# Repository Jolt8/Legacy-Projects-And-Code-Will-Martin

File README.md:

# A Repo for personal projects 

This is a repo for all the pieces of code I've written while learning chemical engineering.

Many of my python projects are quite old as I have switched to Julia. 

The only thing I haven't ported to Julia from python is my old and incomplete process simulator and my MESH distillation solver. 

Most of the work I've done recently has revolved around solving ODEs, PDEs in Julia as well as working ModelingToolkit.jl

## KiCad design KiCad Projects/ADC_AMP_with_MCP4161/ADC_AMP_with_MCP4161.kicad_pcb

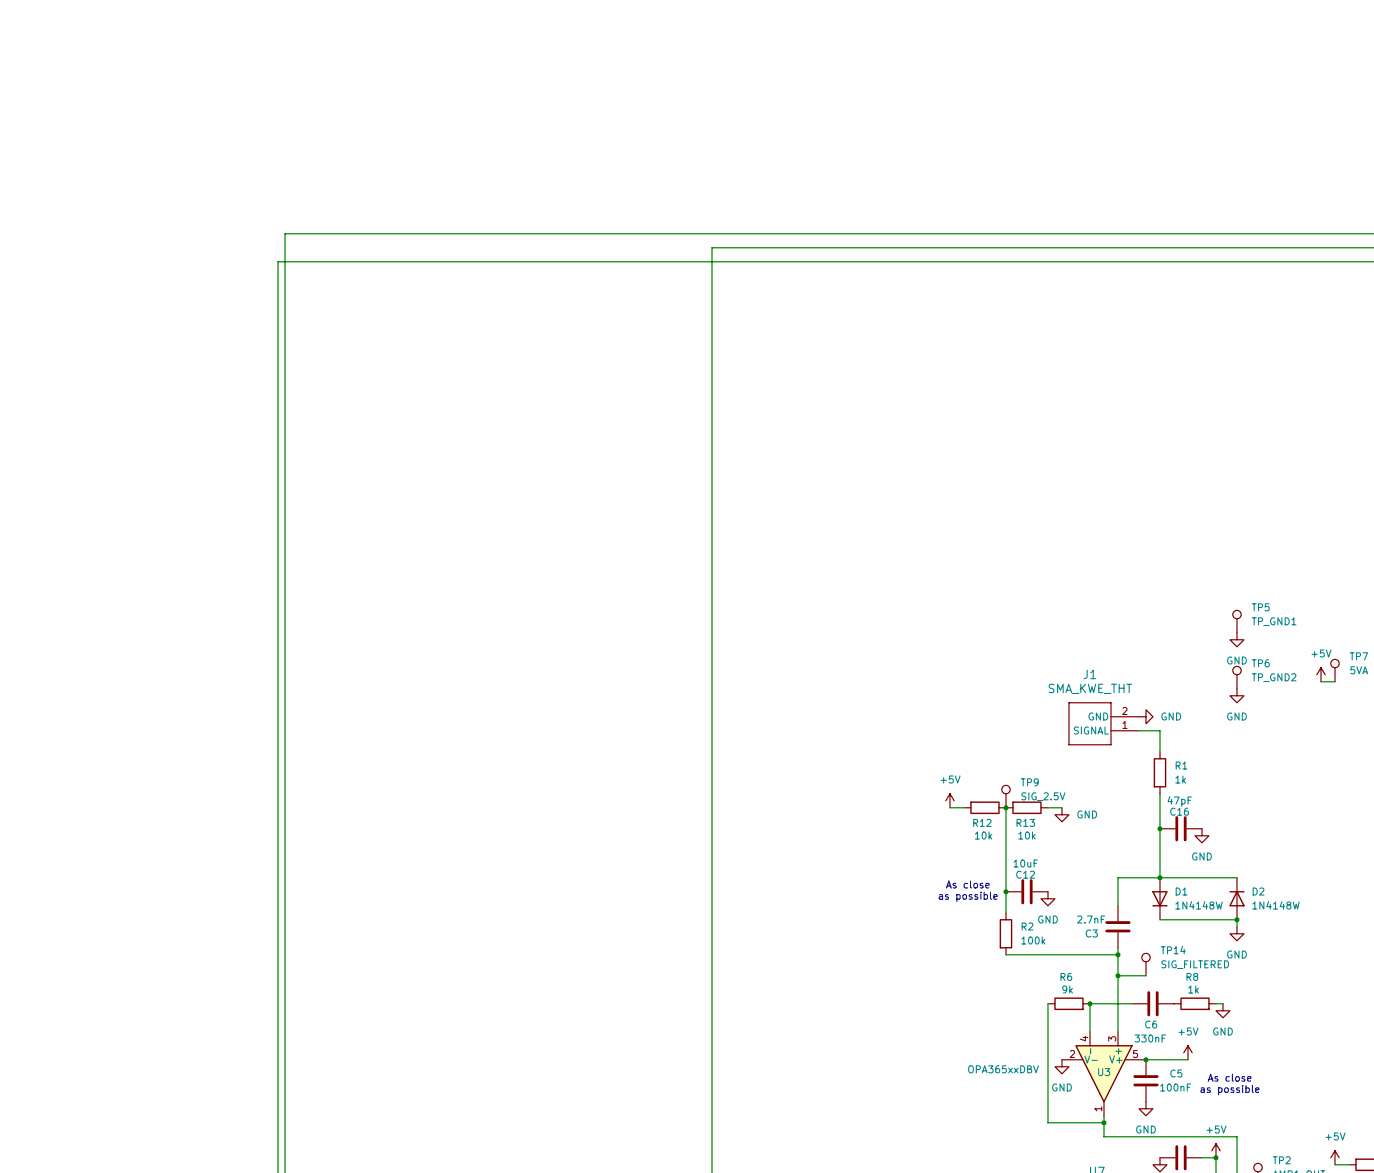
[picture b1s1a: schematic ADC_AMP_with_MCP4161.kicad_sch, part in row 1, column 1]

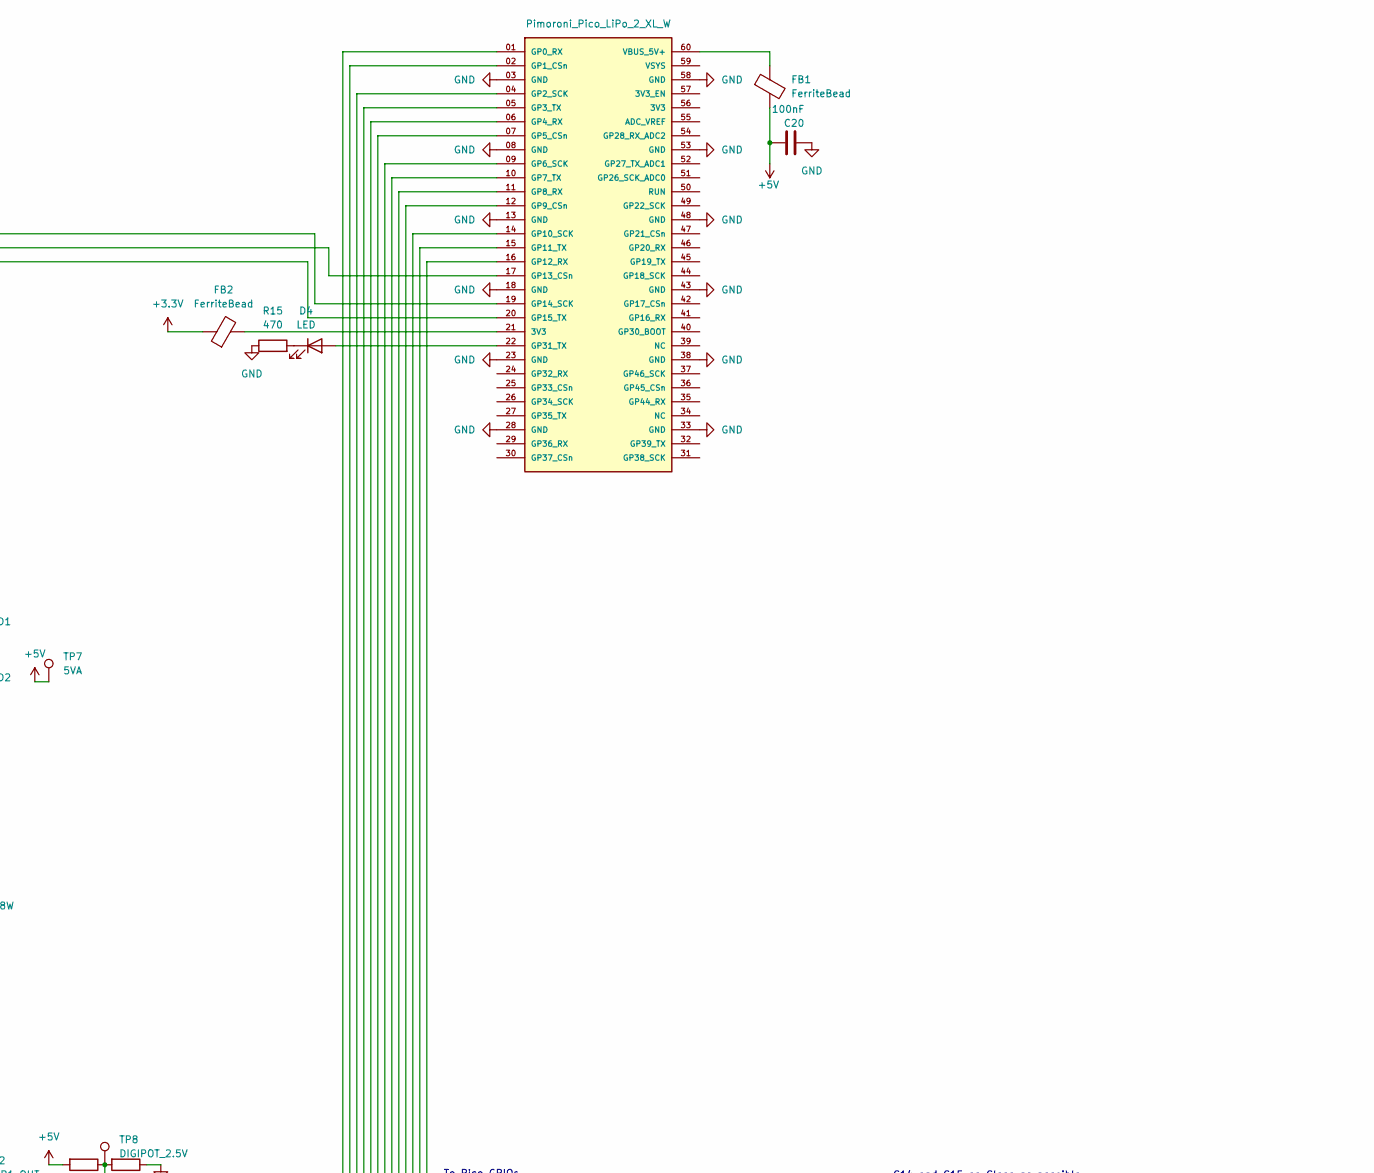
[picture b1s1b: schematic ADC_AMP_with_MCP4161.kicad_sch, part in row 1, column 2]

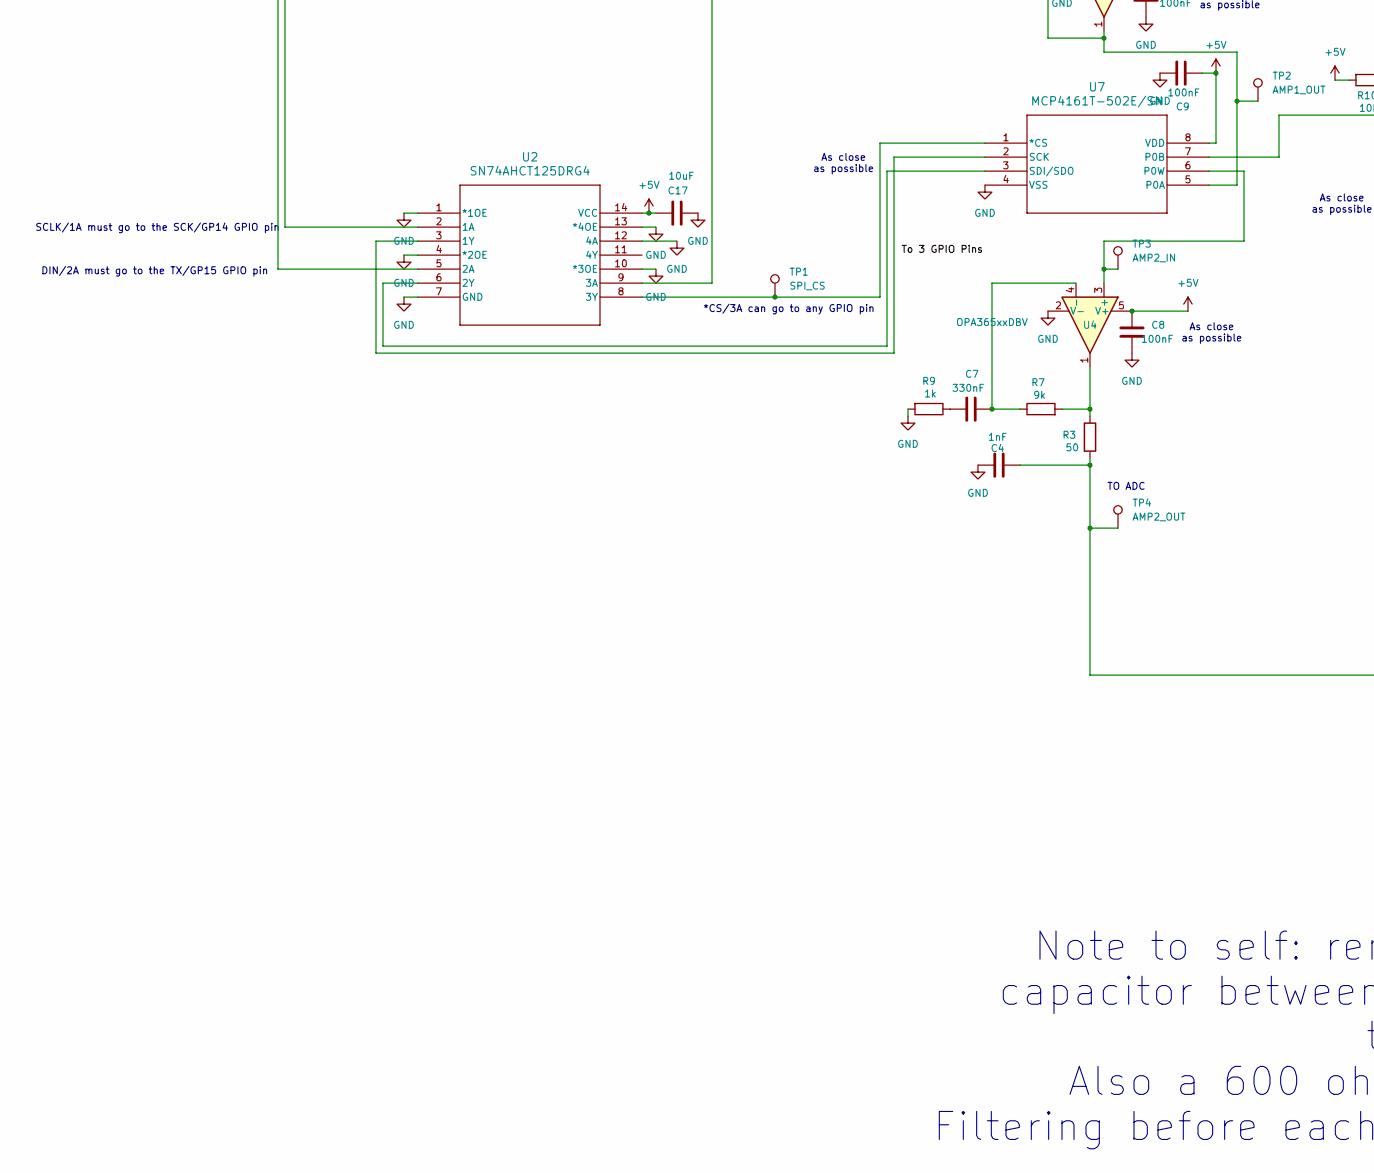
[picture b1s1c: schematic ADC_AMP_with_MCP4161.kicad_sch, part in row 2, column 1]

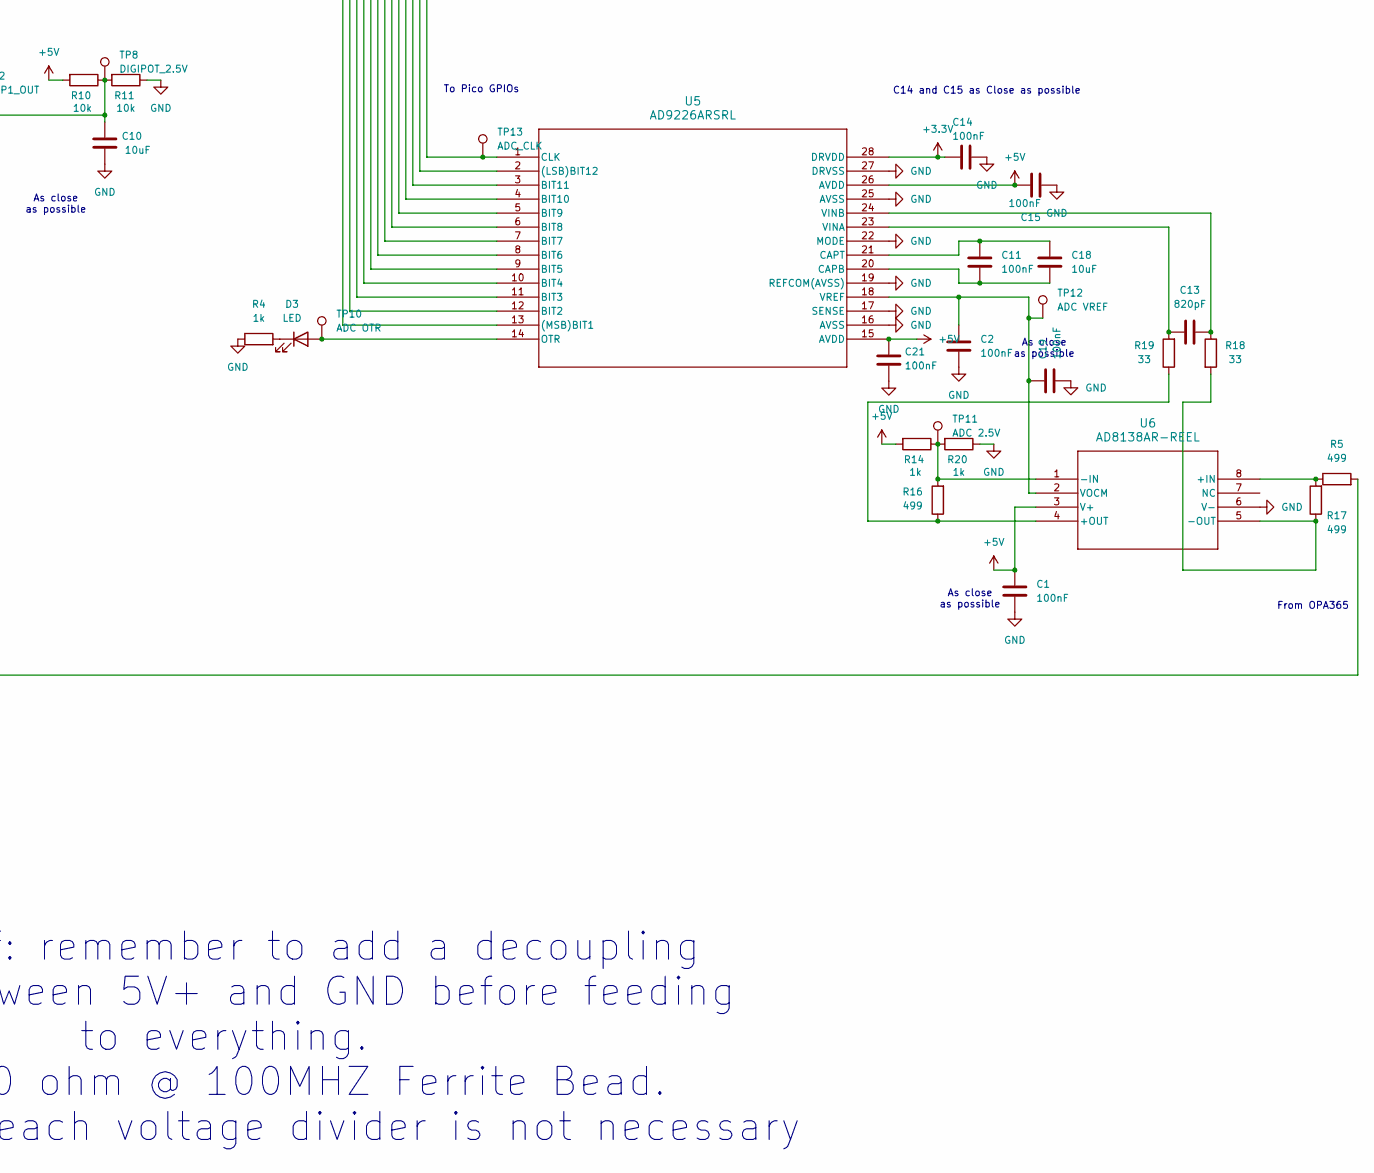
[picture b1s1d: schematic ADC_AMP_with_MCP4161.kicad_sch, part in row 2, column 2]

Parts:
C1, C2, C5, C8, C9, C11, C14, C15, C19, C20, C21: 100nF; C_1206_3216Metric
C3: 2.7nF; C_0603_1608Metric
C4: 1nF; C_0603_1608Metric
C6, C7: 330nF; C_1206_3216Metric
C10, C12, C17, C18: 10uF; C_0805_2012Metric
C13: 820pF; C_0603_1608Metric
C16: 47pF; C_0603_1608Metric
D1, D2: 1N4148W; D_SOD-123
D3, D4: LED; LED_0603_1608Metric
FB1, FB2: FerriteBead; L_0805_2012Metric
J1: SMA_KWE_THT; SMA_KWE
J2: Pimoroni_Pico_LiPo_2_XL_W; Pimoroni Pico LiPo 2 XL W (Staggered pins)
R1: 1k; R_0805_2012Metric
R2: 100k; R_0603_1608Metric
R3: 50; R_0603_1608Metric
R4, R8, R9, R14, R20: 1k; R_0603_1608Metric
R5, R16, R17: 499; R_0603_1608Metric
R6, R7: 9k; R_0603_1608Metric
R10, R11, R12, R13: 10k; R_0603_1608Metric
R15: 470; R_0603_1608Metric
R18, R19: 33; R_0603_1608Metric
TP1: SPI_CS; TestPoint_Loop_D2.50mm_Drill1.0mm
TP2: AMP1_OUT; TestPoint_Loop_D2.50mm_Drill1.0mm
TP3: AMP2_IN; TestPoint_Loop_D2.50mm_Drill1.0mm
TP4: AMP2_OUT; TestPoint_Loop_D2.50mm_Drill1.0mm
TP5: TP_GND1; TestPoint_Loop_D2.50mm_Drill1.0mm
TP6: TP_GND2; TestPoint_Loop_D2.50mm_Drill1.0mm
TP7: 5VA; TestPoint_Loop_D2.50mm_Drill1.0mm
TP8: DIGIPOT_2.5V; TestPoint_Loop_D2.50mm_Drill1.0mm
TP9: SIG_2.5V; TestPoint_Loop_D2.50mm_Drill1.0mm
TP10: ADC OTR; TestPoint_Loop_D2.50mm_Drill1.0mm
TP11: ADC 2.5V; TestPoint_Loop_D2.50mm_Drill1.0mm
TP12: ADC VREF; TestPoint_Loop_D2.50mm_Drill1.0mm
TP13: ADC_CLK; TestPoint_Loop_D2.50mm_Drill1.0mm
TP14: SIG_FILTERED; TestPoint_Loop_D2.50mm_Drill1.0mm
U2: SN74AHCT125DRG4; D14_TEX
U3, U4: OPA365xxDBV; SOT-23-5
U5: AD9226ARSRL; RS_28_ADI
U6: AD8138AR-REEL; R_8_ADI
U7: MCP4161T-502E/SN; SOIC8-N_MC_MCH

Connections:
+3.3V: C14.1, FB2.1, U5.28 (DRVDD)
+5V: C1.1, C5.2, C8.2, C9.1, C15.1, C17.2, C20.1, C21.1, FB1.2, R10.2, R12.2, R14.2, TP7.1 (1_1), U2.14 (VCC), U3.5 (V+), U4.5 (V+), U5.15 (AVDD), U5.26 (AVDD), U6.3 (V+), U7.8 (VDD)
GND: C1.2, C2.2, C4.2, C5.1, C8.1, C9.2, C10.1, C12.1, C14.2, C15.2, C16.1, C17.1, C19.2, C20.2, C21.2, D1.1 (K), D2.2 (A), J1.2 (GND), J2.03 (GND), J2.08 (GND), J2.13 (GND), J2.18 (GND), J2.23 (GND), J2.28 (GND), J2.33 (GND), J2.38 (GND), J2.43 (GND), J2.48 (GND), J2.53 (GND), J2.58 (GND), R4.1, R8.2, R9.2, R11.1, R13.1, R15.1, R20.1, TP5.1 (1_1), TP6.1 (1_1), U2.1 (*1OE), U2.4 (*2OE), U2.7 (GND), U2.10 (*3OE), U2.12 (4A), U2.13 (*4OE), U3.2 (V-), U4.2 (V-), U5.16 (AVSS), U5.17 (SENSE), U5.19 (REFCOM(AVSS)), U5.22 (MODE), U5.25 (AVSS), U5.27 (DRVSS), U6.6 (V-), U7.4 (VSS)
unnamed: C4.1, R3.2, R5.2, TP4.1 (1_1)
unnamed: C6.1, R8.1
unnamed: C7.1, R9.1
unnamed: C12.2, R2.1, R12.1, R13.2, TP9.1 (1_1)
unnamed: C3.2, C16.2, D1.2 (A), D2.1 (K), R1.2
unnamed: D3.2 (A), TP10.1 (1_1), U5.14 (OTR)
unnamed: D3.1 (K), R4.2
unnamed: D4.2 (A), J2.22 (GP31_TX)
unnamed: D4.1 (K), R15.2
unnamed: FB2.2, J2.21 (3V3)
unnamed: J1.1 (SIGNAL), R1.1
unnamed: J2.01 (GP0_RX), U5.13 ((MSB)BIT1)
unnamed: J2.02 (GP1_CSn), U5.12 (BIT2)
unnamed: J2.04 (GP2_SCK), U5.11 (BIT3)
unnamed: J2.05 (GP3_TX), U5.10 (BIT4)
unnamed: J2.06 (GP4_RX), U5.9 (BIT5)
unnamed: J2.07 (GP5_CSn), U5.8 (BIT6)
unnamed: J2.09 (GP6_SCK), U5.7 (BIT7)
unnamed: J2.10 (GP7_TX), U5.6 (BIT8)
unnamed: J2.11 (GP8_RX), U5.5 (BIT9)
unnamed: J2.12 (GP9_CSn), U5.4 (BIT10)
unnamed: J2.14 (GP10_SCK), U5.3 (BIT11)
unnamed: J2.15 (GP11_TX), U5.2 ((LSB)BIT12)
unnamed: J2.16 (GP12_RX), TP13.1 (1_1), U5.1 (CLK)
unnamed: J2.17 (GP13_CSn), U2.9 (3A)
unnamed: J2.19 (GP14_SCK), U2.2 (1A)
unnamed: J2.20 (GP15_TX), U2.5 (2A)
unnamed: FB1.1, J2.60 (VBUS_5V+)
unnamed: R3.1, R7.2, U4.1
unnamed: U2.3 (1Y), U7.2 (SCK)
unnamed: U2.6 (2Y), U7.3 (SDI/SDO)
unnamed: TP1.1 (1_1), U2.8 (3Y), U7.1 (*CS)
unnamed: C3.1, R2.2, TP14.1 (1_1), U3.3 (+)
unnamed: C6.2, R6.2, U3.4 (-)
unnamed: TP3.1 (1_1), U4.3 (+), U7.6 (P0W)
unnamed: C7.2, R7.1, U4.4 (-)
unnamed: C11.2, C18.2, U5.20 (CAPB)
unnamed: C11.1, C18.1, U5.21 (CAPT)
unnamed: C13.1, R19.2, U5.23 (VINA)
unnamed: C13.2, R18.1, U5.24 (VINB)
unnamed: C2.1, C19.1, TP12.1 (1_1), U5.18 (VREF), U6.2 (VOCM)
unnamed: R5.1, R17.2, U6.8 (+IN)
unnamed: R16.1, R19.1, U6.4 (+OUT)
unnamed: R14.1, R16.2, R20.2, TP11.1 (1_1), U6.1 (-IN)
unnamed: R17.1, R18.2, U6.5 (-OUT)
unnamed: R6.1, TP2.1 (1_1), U3.1, U7.5 (P0A)
unnamed: C10.2, R10.1, R11.2, TP8.1 (1_1), U7.7 (P0B)

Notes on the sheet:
To Pico GPIOs
As close as possible
*CS/3A can go to any GPIO pin
C14 and C15 as Close as possible
SCLK/1A must go to the SCK/GP14 GPIO pin
DIN/2A must go to the TX/GP15 GPIO pin
From OPA365
Note to self: remember to add a decoupling capacitor between 5V+ and GND before feeding to everything. Also a 600 ohm @ 100MHZ Ferrite Bead. Filtering before each voltage divider is not necessary
TO ADC

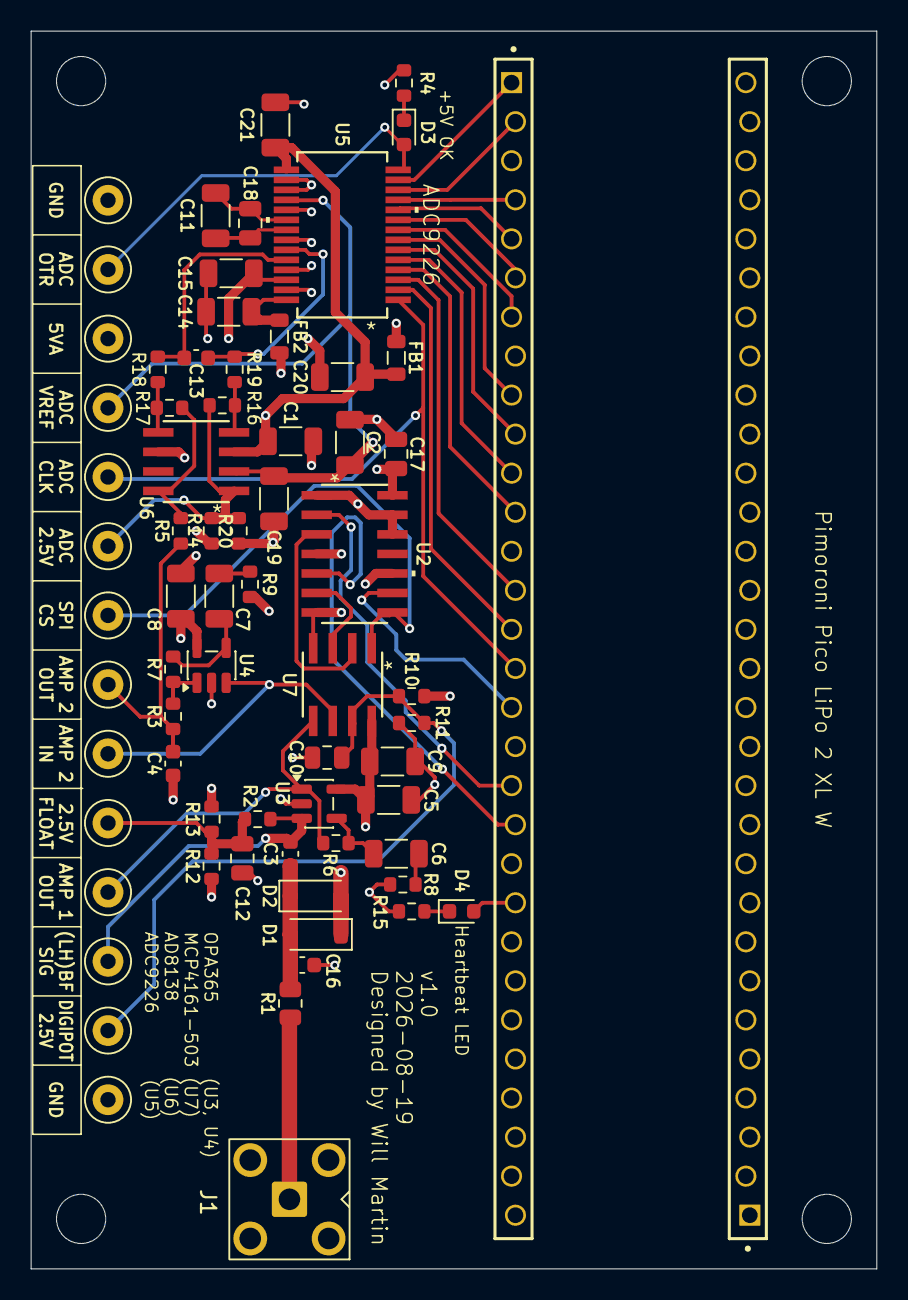
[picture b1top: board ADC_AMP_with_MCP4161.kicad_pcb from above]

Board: 4 copper layers, 55.0 x 80.5 mm, 69 parts (0 on the bottom side), 50 nets.

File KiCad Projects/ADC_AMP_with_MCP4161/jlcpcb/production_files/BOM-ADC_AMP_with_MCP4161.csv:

Comment,Designator,Footprint,LCSC,Quantity
100k,R2,R_0603_1608Metric,C25803,1
100nF,"C1,C11,C14,C15,C19,C2,C20,C21,C5,C8,C9",C_1206_3216Metric,C24497,11
10k,"R10,R11,R12,R13",R_0603_1608Metric,C25804,4
10uF,"C10,C12,C17,C18",C_0805_2012Metric,C15850,4
1N4148W,"D1,D2",D_SOD-123,C81598,2
1k,R1,R_0805_2012Metric,C17513,1
1k,"R14,R20,R4,R8,R9",R_0603_1608Metric,C21190,5
1nF,C4,C_0603_1608Metric,C1588,1
2.7nF,C3,C_0603_1608Metric,C77034,1
33,"R18,R19",R_0603_1608Metric,C23140,2
330nF,"C6,C7",C_1206_3216Metric,C3837965,2
470,R15,R_0603_1608Metric,C23179,1
47pF,C16,C_0603_1608Metric,C1671,1
499,"R16,R17,R5",R_0603_1608Metric,C19686428,3
50,R3,R_0603_1608Metric,C849792,1
5VA,TP7,TestPoint_Loop_D2.50mm_Drill1.0mm,C5199801,1
820pF,C13,C_0603_1608Metric,C597178,1
9k,"R6,R7",R_0603_1608Metric,C6792189,2
AD8138AR-REEL,U6,R_8_ADI,C113762,1
AD9226ARSRL,U5,RS_28_ADI,C730053,1
ADC 2.5V,TP11,TestPoint_Loop_D2.50mm_Drill1.0mm,C5199801,1
ADC OTR,TP10,TestPoint_Loop_D2.50mm_Drill1.0mm,C5199801,1
ADC VREF,TP12,TestPoint_Loop_D2.50mm_Drill1.0mm,C5199801,1
ADC_CLK,TP13,TestPoint_Loop_D2.50mm_Drill1.0mm,C5199801,1
AMP1_OUT,TP2,TestPoint_Loop_D2.50mm_Drill1.0mm,C5199801,1
AMP2_IN,TP3,TestPoint_Loop_D2.50mm_Drill1.0mm,C5199801,1
AMP2_OUT,TP4,TestPoint_Loop_D2.50mm_Drill1.0mm,C5199801,1
DIGIPOT_2.5V,TP8,TestPoint_Loop_D2.50mm_Drill1.0mm,C5199801,1
FerriteBead,"FB1,FB2",L_0805_2012Metric,C48543403,2
LED,"D3,D4",LED_0603_1608Metric,C2286,2
MCP4161T-502E/SN,U7,SOIC8-N_MC_MCH,C620268,1
OPA365xxDBV,"U3,U4",SOT-23-5,C96626,2
SIG_2.5V,TP9,TestPoint_Loop_D2.50mm_Drill1.0mm,C5199801,1
SIG_FILTERED,TP14,TestPoint_Loop_D2.50mm_Drill1.0mm,C5199801,1
SMA_KWE_THT,J1,SMA_KWE,C496551,1
SN74AHCT125DRG4,U2,D14_TEX,C155176,1
SPI_CS,TP1,TestPoint_Loop_D2.50mm_Drill1.0mm,C5199801,1
TP_GND1,TP5,TestPoint_Loop_D2.50mm_Drill1.0mm,C5199801,1
TP_GND2,TP6,TestPoint_Loop_D2.50mm_Drill1.0mm,C5199801,1
Pimoroni_Pico_LiPo_2_XL_W,J2,Pimoroni Pico LiPo 2 XL W (Staggered pins),,1

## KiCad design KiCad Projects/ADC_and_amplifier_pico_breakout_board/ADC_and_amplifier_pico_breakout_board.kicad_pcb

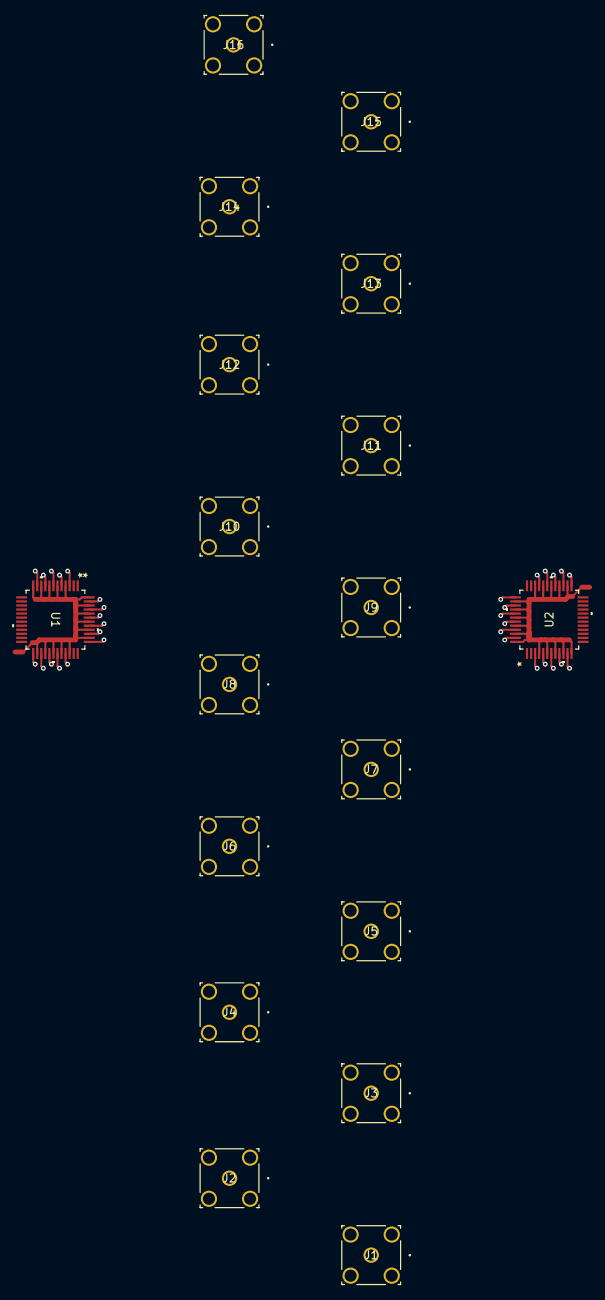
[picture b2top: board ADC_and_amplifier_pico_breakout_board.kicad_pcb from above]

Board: 2 copper layers, 18 parts (0 on the bottom side), 19 nets.

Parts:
J1, J2, J3, J4, J5, J6, J7, J8, J9, J10, J11, J12, J13, J14, J15, J16: CONREVSMA001-G; COAX4GND_CONREVSMA001-G_TEC
U1, U2: HV2707T-C/R8X; LQFP48_R8_MCH

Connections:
unnamed: J1.2 (GND), J1.3 (GND), J1.4 (GND), J1.5 (GND), J2.2 (GND), J2.3 (GND), J2.4 (GND), J2.5 (GND), J3.2 (GND), J3.3 (GND), J3.4 (GND), J3.5 (GND), J4.2 (GND), J4.3 (GND), J4.4 (GND), J4.5 (GND), J5.2 (GND), J5.3 (GND), J5.4 (GND), J5.5 (GND), J6.2 (GND), J6.3 (GND), J6.4 (GND), J6.5 (GND), J7.2 (GND), J7.3 (GND), J7.4 (GND), J7.5 (GND), J8.2 (GND), J8.3 (GND), J8.4 (GND), J8.5 (GND), J9.2 (GND), J9.3 (GND), J9.4 (GND), J9.5 (GND), J10.2 (GND), J10.3 (GND), J10.4 (GND), J10.5 (GND), J11.2 (GND), J11.3 (GND), J11.4 (GND), J11.5 (GND), J12.2 (GND), J12.3 (GND), J12.4 (GND), J12.5 (GND), J13.2 (GND), J13.3 (GND), J13.4 (GND), J13.5 (GND), J14.2 (GND), J14.3 (GND), J14.4 (GND), J14.5 (GND), J15.2 (GND), J15.3 (GND), J15.4 (GND), J15.5 (GND), J16.2 (GND), J16.3 (GND), J16.4 (GND), J16.5 (GND)
unnamed: J1.1 (SIGNAL), U1.25 (SW15B), U2.12 (SW0A)
unnamed: J2.1 (SIGNAL), U1.27 (SW14B), U2.10 (SW1A)
unnamed: J3.1 (SIGNAL), U1.29 (SW13B), U2.8 (SW2A)
unnamed: J4.1 (SIGNAL), U1.31 (SW12B), U2.6 (SW3A)
unnamed: J5.1 (SIGNAL), U1.33 (SW11B), U2.4 (SW4A)
unnamed: J6.1 (SIGNAL), U1.37 (SW10B), U2.48 (SW5A)
unnamed: J7.1 (SIGNAL), U1.39 (SW9B), U2.46 (SW6A)
unnamed: J8.1 (SIGNAL), U1.41 (SW8B), U2.44 (SW7A)
unnamed: J9.1 (SIGNAL), U1.43 (SW7B), U2.42 (SW8A)
unnamed: J10.1 (SIGNAL), U1.45 (SW6B), U2.40 (SW9A)
unnamed: J11.1 (SIGNAL), U1.47 (SW5B), U2.38 (SW10A)
unnamed: J12.1 (SIGNAL), U1.3 (SW4B), U2.34 (SW11A)
unnamed: J13.1 (SIGNAL), U1.5 (SW3B), U2.32 (SW12A)
unnamed: J14.1 (SIGNAL), U1.7 (SW2B), U2.30 (SW13A)
unnamed: J15.1 (SIGNAL), U1.9 (SW1B), U2.28 (SW14A)
unnamed: J16.1 (SIGNAL), U1.11 (SW0B), U2.26 (SW15A)
unnamed: U1.4 (SW4A), U1.6 (SW3A), U1.8 (SW2A), U1.10 (SW1A), U1.12 (SW0A), U1.26 (SW15A), U1.28 (SW14A), U1.30 (SW13A), U1.32 (SW12A), U1.34 (SW11A), U1.38 (SW10A), U1.40 (SW9A), U1.42 (SW8A), U1.44 (SW7A), U1.46 (SW6A), U1.48 (SW5A)
unnamed: U2.3 (SW4B), U2.5 (SW3B), U2.7 (SW2B), U2.9 (SW1B), U2.11 (SW0B), U2.25 (SW15B), U2.27 (SW14B), U2.29 (SW13B), U2.31 (SW12B), U2.33 (SW11B), U2.37 (SW10B), U2.39 (SW9B), U2.41 (SW8B), U2.43 (SW7B), U2.45 (SW6B), U2.47 (SW5B)

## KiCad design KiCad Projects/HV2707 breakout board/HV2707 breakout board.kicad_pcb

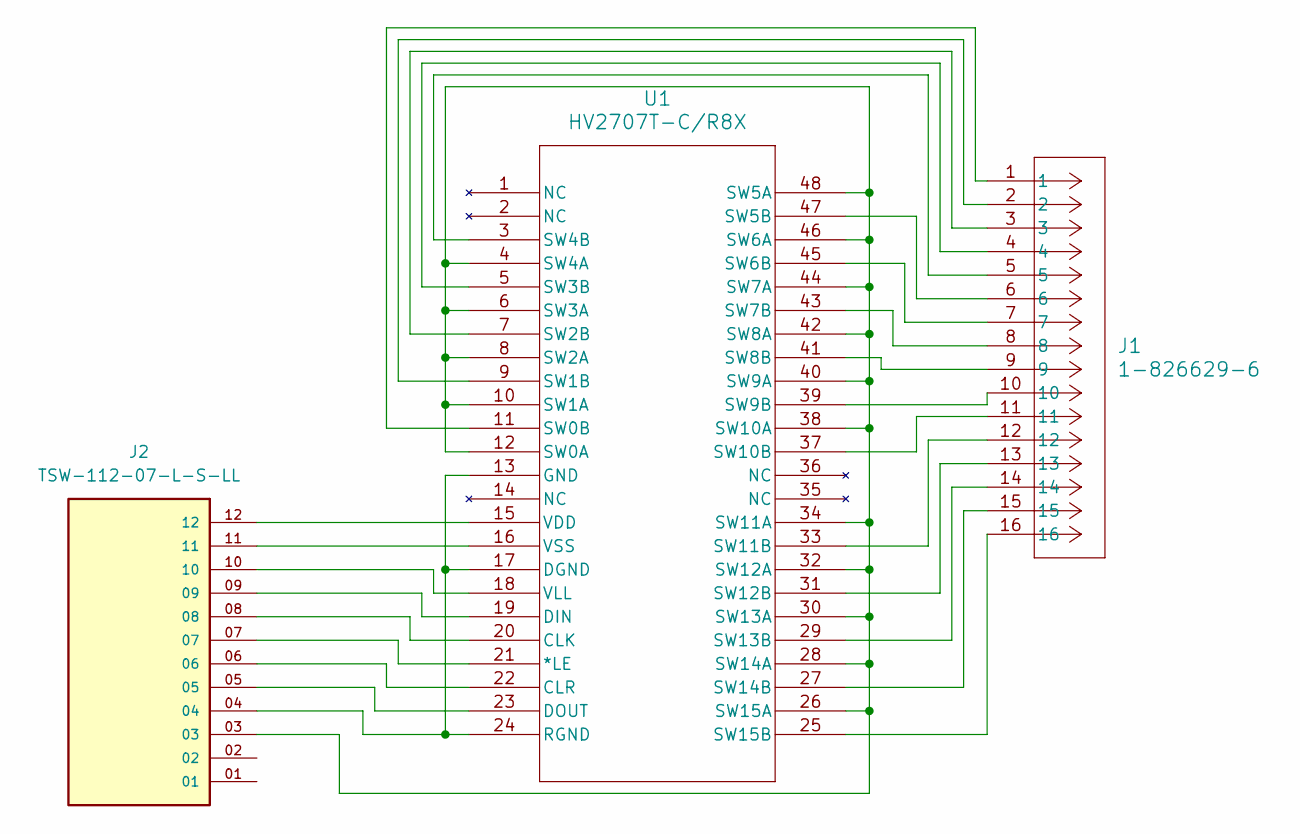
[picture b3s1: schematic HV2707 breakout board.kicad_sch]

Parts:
J1: 1-826629-6; CON16_1X16_P100UM_HDR_TYC
J2: TSW-112-07-L-S-LL; SAMTEC_TSW-112-07-L-S-LL; PARTREV R
U1: HV2707T-C/R8X; LQFP48_R8_MCH

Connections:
unnamed: J2.07, U1.21 (*LE)
unnamed: J2.08, U1.20 (CLK)
unnamed: J2.06, U1.22 (CLR)
unnamed: J2.04, U1.13 (GND), U1.17 (DGND), U1.24 (RGND)
unnamed: J2.09, U1.19 (DIN)
unnamed: J2.05, U1.23 (DOUT)
unnamed: J2.03, U1.4 (SW4A), U1.6 (SW3A), U1.8 (SW2A), U1.10 (SW1A), U1.12 (SW0A), U1.26 (SW15A), U1.28 (SW14A), U1.30 (SW13A), U1.32 (SW12A), U1.34 (SW11A), U1.38 (SW10A), U1.40 (SW9A), U1.42 (SW8A), U1.44 (SW7A), U1.46 (SW6A), U1.48 (SW5A)
unnamed: J1.1, U1.11 (SW0B)
unnamed: J1.2, U1.9 (SW1B)
unnamed: J1.3, U1.7 (SW2B)
unnamed: J1.4, U1.5 (SW3B)
unnamed: J1.5, U1.3 (SW4B)
unnamed: J1.6, U1.47 (SW5B)
unnamed: J1.7, U1.45 (SW6B)
unnamed: J1.8, U1.43 (SW7B)
unnamed: J1.9, U1.41 (SW8B)
unnamed: J1.10, U1.39 (SW9B)
unnamed: J1.11, U1.37 (SW10B)
unnamed: J1.12, U1.33 (SW11B)
unnamed: J1.13, U1.31 (SW12B)
unnamed: J1.14, U1.29 (SW13B)
unnamed: J1.15, U1.27 (SW14B)
unnamed: J1.16, U1.25 (SW15B)
unnamed: J2.12, U1.15 (VDD)
unnamed: J2.10, U1.18 (VLL)
unnamed: J2.11, U1.16 (VSS)

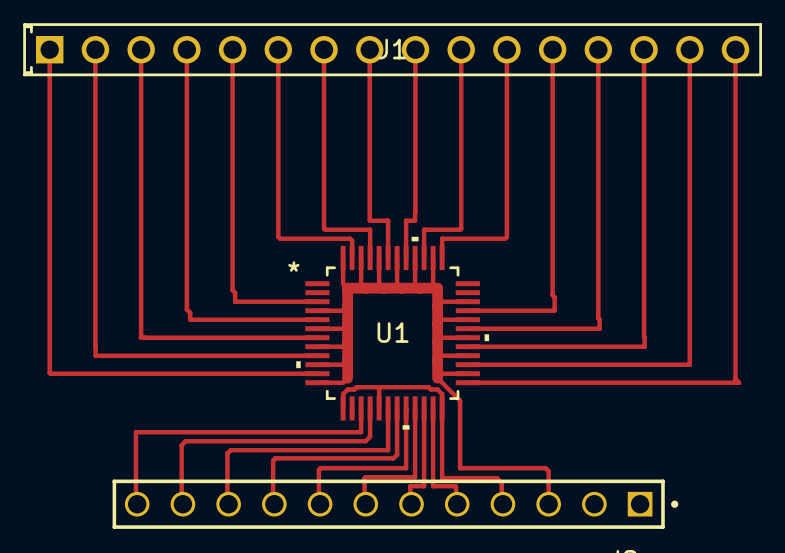
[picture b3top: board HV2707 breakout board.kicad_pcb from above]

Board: 2 copper layers, 3 parts (0 on the bottom side), 26 nets.

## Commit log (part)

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2025-11-02 Didn't know why I still had that there
2025-11-02 Recommiting before purge for gitignore
2025-11-02 Purging all files for gitgore
2025-11-06 Used Gemini to help with using GLMakie for for future work
2025-11-08 Trying to test out mtkmodels, it's not going great
2025-11-08 Huh, I guess PDEs do work with mtkmodels to some extent
2025-11-08 Ok, this looks pretty promising for doing PDEs with Acusal modeling. Used Gemini for most of this but I just wanted to hammer out an example to use for future work.
2025-11-08 Created a new file for a 2D PDE case for mtkcomponents, it works well, but my GLMakie implementation still needs work
2025-11-10 I hate debugging modelingtoolkit
2025-11-12 Finally got MTK to play nice, only structural simplify fails now.
2025-11-12 Creating a new file to prevent messing up the previous one
2025-11-17 Updating the name
2025-11-19 Created a function for getting the unique connections between cells in a grid
2025-11-19 changed function name a little
2025-11-19 Getting closer to finishing this even though I'm doubting its scalability
2025-11-19 created a seperate timing file for future sims
2025-11-19 That timing file was pretty useless
2025-11-19 Created a 3D version of FEM with mtkcomponents
2025-11-20 Even the example in the docs doesn't work for symbolic arrays. I will never understand symbolic vectors
2025-11-24 Cleaning this up a bit
2025-11-24 Very minimal changes on all of these
2025-11-24 Ok I had Gemini write a non-mtkcomponent version of my FVM with mtkcomponents just to test the performance and holy shit this is BLAZINGLY fast. A 1 million cell system took 10 seconds to run on a i7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
2025-11-25 Oops, looks like Ferrite can already export to VTK without me having to write anything manually, what a relief. I'll still keep Testing WriteVTK if I need to reference it in the future.
2025-11-27 I've done a lot of work to make this type of workflow more generlizable and I'm pretty close to getting something really good. Currently, Generalized Manual ODE FVM without Unitful is the most advanc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
2025-11-28 Created explicit (non-matrix) and implicit (matrix) versions of the FVM workflow, I will probably mainly be updating the matrix one in the future. Generalized Manual ODE FVM will be deleted but it's 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
